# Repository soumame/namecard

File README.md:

# NFC Namecard/Badge

NFCによる給電（Energy Harvesting）を用いた、書き換え可能な電子ペーパー / NFCタグ / マイコンと、ファームウェア、Android・iOSアプリです。

Maker Faire Tokyo 2026のブース「そうまめの部屋」向けに製作しました。

## リポジトリ構成

- `namecard.kicad_sch` / `namecard.kicad_pcb` — KiCad回路図・基板設計
- [`production/`](production/) — Gerber、BOM、CPLなどの製造データ
- [`firmware/`](firmware/) — STM32ファームウェア
- [`client/android/`](client/android/) — Androidアプリ
- [`client/ios/`](client/ios/) — iOSアプリ（TestFlightベータ配布）
- [`iOS_development.md`](iOS_development.md) — iOS版の実装構成と今後の検証計画

Maker Faire Tokyo 2026向けの現行製造データは[`production/v5/`](production/v5/)にあります。JLCPCBへ入稿するファイルと注意点は同ディレクトリのREADMEを確認してください。

## Androidアプリのインストール

**[最新版のAndroidアプリ（namecard.apk）をダウンロード](https://github.com/soumame/namecard/releases/download/android-main/namecard.apk)**

利用にはAndroid 8.0以降のNFC対応端末が必要です。

1. 上のリンクから`namecard.apk`をダウンロードする
2. ブラウザからのインストールが止められた場合は、表示された設定画面で今回使用したブラウザからのインストールを許可する
3. 設定画面から戻り、`namecard.apk`をインストールする
4. インストール後、必要に応じてブラウザからのインストール許可をOFFへ戻す
5. アプリを開き、画像やテキストを編集してから`NFCに書込`を選び、完了するまで名刺を端末のNFCアンテナへ固定する

アップデートするときは、最新版APKを再度ダウンロードして既存アプリの上からインストールしてください。アプリを先にアンインストールすると、Libraryに保存した画像も削除されます。

このアプリが要求するAndroid権限はNFCのみです。リリースにはAPKと一緒にSHA-256チェックサムを掲載しています。[Releases](https://github.com/soumame/namecard/releases)の`android-main`は最新版で上書きされます。ソースの変更履歴は[コミット一覧](https://github.com/soumame/namecard/commits/main/)で確認できます。

うまく書き込めない場合は、スマートフォンのNFCアンテナ位置を確認し、ケースを外してからもう一度お試しください。書き込み中は名刺を動かしたり、ほかのアプリへ切り替えたりしないでください。

## iOSアプリ

iOS 17以降のNFC対応iPhone向けに、MameCardをTestFlightでベータ配布しています。

**[TestFlight事前登録フォームに回答する](https://forms.gle/RqQPmfoJ9aMMtRm66)**

フォームへの回答後に、TestFlightの参加リンクをお送りします。届いたリンクから案内に沿って
インストールしてください。名刺への書き込みには対応する名刺基板が必要です。

iPhone XR／iOS 18で白黒画像・URL設定・クリーニング・振動案内の動作報告を受けています。
ほかの機種での確認と給電・時間の計測を進めます。試す内容と報告方法は
[ベータ試験ガイド](client/ios/docs/BETA_TESTING.md)を参照してください。

4階調は編集・プレビュー・保存・BIN入出力に対応しますが、iOSからの4階調NFC書き込みと、
4階調表示からの白黒移行は無効です。販売済みの基板・FWの変更は不要です。
開発・配布の手順は[iOSアプリのREADME](client/ios/README.md)を参照してください。

## 開発状況について

詳しい開発状況は[ブログ記事](https://tokumaru.work/ja/tech/maker-faire-tokyo-2026/)をご確認ください。

## Q&A

### なんでアプリがPlay Storeで公開されていないの?

- 少量製作のハードウェア向けアプリであるため、現在は署名済みAPKをGitHub Releasesで公開しています。
- ソースコードもこのリポジトリで確認できます。

### iOS版はいつ使えるの?

- TestFlightでベータ版を利用できます。[事前登録フォーム](https://forms.gle/RqQPmfoJ9aMMtRm66)への回答後に、TestFlightの参加リンクをお送りします。実機検証後にApp Store公開を目指します。
- Apple Developer Programには登録済みです。現在の配布手順は[iOS配布ドキュメント](client/ios/docs/DISTRIBUTION.md)を参照してください。

### 1枚あたりの原価は？いくらで売るの？

- 部品の調達や製品の仕様次第ですが、30枚量産すると1枚あたり2500~3000円超えとなります。
  - たくさん発注すれば安くなるので、大量生産すれば2000~2500円くらいを狙えると考えています。
- それに自分の開発に使う道具の調達や時間を入れると、5000円くらいで売るのが妥当かなと考えています。

## ライセンス

このリポジトリで独自に作成したハードウェア設計、製造データ、ファームウェア、Android・iOSアプリ、文書は[MIT License](LICENSE)で提供します。自由に利用・改変・再配布できますが、著作権表示とライセンス表示を保持してください。

STM32Cube/CMSISやMaterial Symbolsなどの第三者著作物には、それぞれのライセンスが適用されます。詳細は[THIRD_PARTY_NOTICES.md](THIRD_PARTY_NOTICES.md)を確認してください。

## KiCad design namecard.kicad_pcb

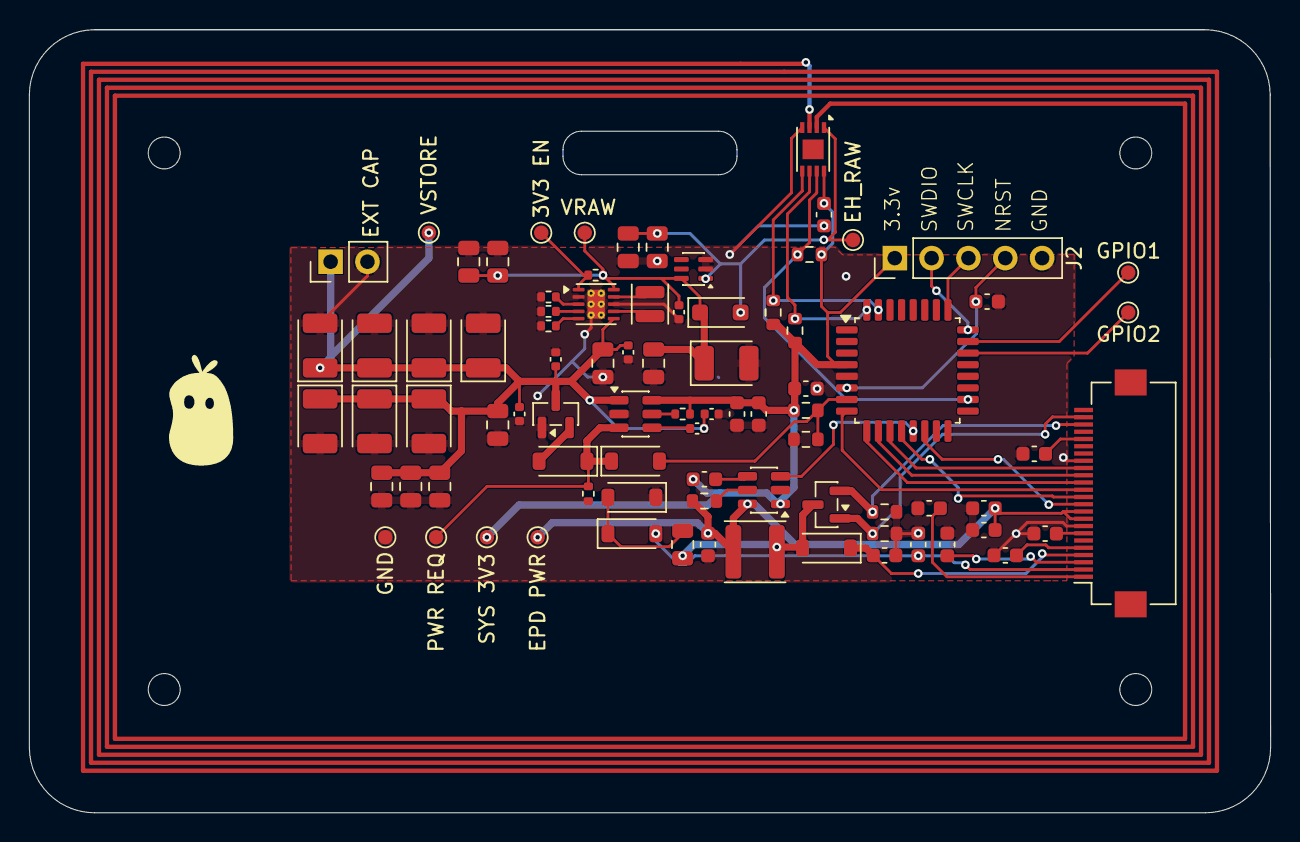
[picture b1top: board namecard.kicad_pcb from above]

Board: 2 copper layers, 85.6 x 54.0 mm, 84 parts (0 on the bottom side), 46 nets.

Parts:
3V3 EN: EN_3V3_TP; TestPoint_Pad_D1.0mm
C1, C2, C5, C6, C7, C9, C10, C11, C12: 1uF 50V X5R; C_0603_1608Metric
C3: 4.7uF 25V X5R; C_0805_2012Metric
C4: 4.7uF 16V X5R; C_0603_1608Metric
C8, C13: 0.1uF; C_0603_1608Metric
C14, C15, C16, C17: 220uF/6.3V; CP_EIA-3528-21_Kemet-B
C18, C20: 100nf; C_0603_1608Metric
C19: 1nF; C_0603_1608Metric
C23, C25: 1uf; C_0805_2012Metric
C24, C26: 0.1uf; C_0805_2012Metric
C27: 1nF; C_0402_1005Metric
C28, C41, C43, C44, C45: 100nF; C_0402_1005Metric
C29, C30, C31, C32, C42: 22uF 6.3V X5R; C_0805_2012Metric
C39: 220uF/6.3V VRAW; CP_EIA-3528-21_Kemet-B
C40: 10uF 25V X5R; C_0805_2012Metric
C46, C48, C49: 220uF/6.3V VRES; CP_EIA-3528-21_Kemet-B
C47: 100nF U2 DECOUPLING; C_0603_1608Metric
D1, D2, D3: MBR0530T1G; D_SOD-123
D4: DNP SCHOTTKY; D_SOD-123F
D5, D6: 1N4148W; D_SOD-123
EPD PWR: EPD_SW_TP; TestPoint_Pad_D1.0mm
EXT CAP: EXT_VRES_CAP_DNP; PinHeader_1x02_P2.54mm_Vertical
GND: TestPoint; TestPoint_Pad_D1.0mm
GPIO1, GPIO2: TestPoint; TestPoint_Pad_D1.0mm
J1: Conn_01x24; Hirose_FH12-24S-0.5SH_1x24-1MP_P0.50mm_Horizontal
J2: Conn_01x05; PinHeader_1x05_P2.54mm_Vertical
L1: 47uH; L_APV_ANR4020
L2: 2.2uH; L_Sunlord_SWPA252012S
PWR REQ: PWR_REQ_TP; TestPoint_Pad_D1.0mm
Q1: AO3400A; SOT-23
R1: 1M; R_0603_1608Metric
R2: 2.2R; R_0603_1608Metric
R3: 1M DNP; R_0603_1608Metric
R4, R6: 10k; R_0603_1608Metric
R5: 470k DNP; R_0603_1608Metric
R7: 4.7M; R_0402_1005Metric
R8: 1k; R_0402_1005Metric
R9: 36.5k 1%; R_0402_1005Metric
R10: 5.11k 1% (2.5mA); R_0402_1005Metric
R11: 16.2k 1%; R_0402_1005Metric
R12: 0R; R_0402_1005Metric
R13: 10k GPO PULLUP; R_0603_1608Metric
R14: 1k EPD DISCHARGE; R_0603_1608Metric
SYS 3V3: SYS_VDD_TP; TestPoint_Pad_D1.0mm
TP1: VRES_3V3_TP; TestPoint_Pad_D1.0mm
TP3: V_EH_RAW_TP; TestPoint_Pad_D1.0mm
U1: STM32G031K8T6; LQFP-32_7x7mm_P0.8mm
U2: ST25DV04K-IER6C3; DFN-8-1EP_3x2mm_P0.5mm_EP1.36x1.46mm
U3, U4: TPS22917DBV; SOT-23-6
U5: TPS3839K33DBZR; SOT-23
U6: LM66100; SOT-363_SC-70-6
U7: TPS63900; WSON-10-1EP_2.5x2.5mm_P0.5mm_EP1.2x2mm_ThermalVias
VRAW: VRAW_TP; TestPoint_Pad_D1.0mm

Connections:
/CFG1: R9.1, U7.3 (CFG1)
/CFG2: R10.1, U7.4 (CFG2)
/CFG3: R11.1, U7.5 (CFG3)
/EN_3V3: 3V3 EN.1 (1_1), R12.2, U7.1 (EN)
/EPD_BUSY: J1.16, U1.11 (PA4)
/EPD_CS: J1.13, U1.8 (PA1)
/EPD_DC: J1.14, U1.9 (PA2)
/EPD_RST: J1.15, U1.10 (PA3)
/EPD_SW: C4.1, C9.1, C18.2, EPD PWR.1 (1_1), J1.9, J1.10, L1.2, R14.2, U3.6 (VOUT)
/GDR: J1.23, Q1.1 (G), R1.1
/I2C_SCL: R6.1, U1.32 (PB8), U2.6 (SCL)
/I2C_SDA: R4.1, U1.31 (PB7), U2.5 (SDA)
/LX1: L2.1, U7.9 (LX1)
/LX2: L2.2, U7.7 (LX2)
/NFC_INT: R13.1, U1.18 (PA8), U2.7 (GPO)
/NRST: C13.1, J2.4, U1.6 (PF2-NRST)
/PREVGH: C5.2, D3.1 (K), J1.4
/PREVGL: C11.1, D1.2 (A), J1.2
/PWR_GOOD: D5.2 (A), U5.2 (~RESET)
/PWR_HOLD: D6.2 (A), R3.2, R5.1, U1.7 (PA0)
/PWR_REQ: D5.1 (K), D6.1 (K), PWR REQ.1 (1_1), R7.1, U4.3 (ON)
/RESE: J1.22, Q1.2 (S), R2.1
/SPI_MOSI: J1.11, U1.14 (PA7)
/SPI_SCK: J1.12, U1.12 (PA5)
/SWCLK: J2.3, U1.25 (PA14)
/SWDIO: J2.2, U1.24 (PA13)
/SYS_VDD: C1.1, C8.1, C19.2, C20.1, C47.1, J2.1, R3.1, R4.2, R6.2, R8.1, R13.2, SYS 3V3.1 (1_1), U1.4 (VDD), U2.8 (VCC), U3.1 (VIN), U4.6 (VOUT)
/U3_CT: C19.1, U3.4 (CT)
/U4_CT: C27.1, U4.4 (CT)
/U4_QOD: R8.2, U4.5 (QOD)
/VRAW: C25.1, C26.1, C39.1, C40.1, C41.1, D4.1 (K), R12.1, U6.6 (VOUT), U7.10 (VIN), VRAW.1 (1_1)
/VRES_3V3: C14.1, C15.1, C16.1, C17.1, C27.2, C28.1, C29.1, C30.1, C31.1, C32.1, C42.1, C43.1, C44.1, C45.1, C46.1, C48.1, C49.1, EXT CAP.1, TP1.1 (1_1), U4.1 (VIN), U5.3 (VDD), U7.6 (VOUT)
/V_EH_RAW: C23.1, C24.1, D4.2 (A), TP3.1 (1_1), U2.1 (V_EH), U6.1 (VIN)
GND: C1.2, C2.2, C4.2, C5.1, C6.2, C7.2, C8.2, C9.2, C10.2, C11.2, C12.1, C13.2, C14.2, C15.2, C16.2, C17.2, C18.1, C20.2, C23.2, C24.2, C25.2, C26.2, C28.2, C29.2, C30.2, C31.2, C32.2, C39.2, C40.2, C41.2, C42.2, C43.2, C44.2, C45.2, C46.2, C47.2, C48.2, C49.2, D2.1 (K), EXT CAP.2, GND.1 (1_1), J1.8, J1.17, J2.5, R1.2, R2.2, R5.2, R7.2, R9.2, R10.2, R11.2, U1.5 (VSS), U2.4 (VSS), U3.2 (GND), U4.2 (GND), U5.1 (GND), U6.2 (GND), U6.3 (~CE), U7.2 (SEL), U7.8 (GND), U7.11 (GND)
unnamed: C3.1, D1.1 (K), D2.2 (A)
unnamed: C3.2, D3.2 (A), L1.1, Q1.3 (D)
unnamed: C12.2, J1.1
unnamed: C10.1, J1.3
unnamed: C7.1, J1.5
unnamed: C6.1, J1.7
unnamed: C2.1, J1.20
unnamed: U1.13 (PA6), U3.3 (ON)
unnamed: GPIO2.1 (1_1), U1.22 (PA9/PA11)
unnamed: GPIO1.1 (1_1), U1.23 (PA10/PA12)
unnamed: U2.2 (AC0), U2.3 (AC1)
unnamed: R14.1, U3.5 (QOD)

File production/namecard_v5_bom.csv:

Designator,Footprint,Quantity,Value,LCSC Part #
"C1, C10, C11, C12, C2, C5, C6, C7, C9",0603,9,1uF 50V X5R,C15849
"C13, C8",0603,2,0.1uF,C14663
"C14, C15, C16, C17",CP_EIA-3528-21_Kemet-B,4,220uF/6.3V,C30242
"C18, C20",0603,2,100nf,C14663
C19,0603,1,1nF,C1588
"C23, C25",0805,2,1uf,C28323
"C24, C26",0805,2,0.1uf,C28233
C27,0402,1,1nF,C1523
"C28, C41, C43, C44, C45",0402,5,100nF,C1525
"C29, C30, C31, C32, C42",0805,5,22uF 6.3V X5R,C5674
C3,0805,1,4.7uF 25V X5R,C722528
C39,CP_EIA-3528-21_Kemet-B,1,220uF/6.3V VRAW,C30242
C4,0603,1,4.7uF 16V X5R,C19666
C40,0805,1,10uF 25V X5R,C5137488
"C46, C48, C49",CP_EIA-3528-21_Kemet-B,3,220uF/6.3V VRES,C30242
C47,0603,1,100nF U2 DECOUPLING,C14663
"D1, D2, D3",D_SOD-123,3,MBR0530T1G,C82046
"D5, D6",D_SOD-123,2,1N4148W,C47117477
J1,Hirose_FH12-24S-0.5SH_1x24-1MP_P0.50mm_Horizontal,1,Conn_01x24,C506794
J2,PinHeader_1x05_P2.54mm_Vertical,1,Conn_01x05,C5156614
L1,L_APV_ANR4020,1,47uH,C6364799
L2,L_Sunlord_SWPA252012S,1,2.2uH,C23894
Q1,SOT-23,1,AO3400A,C20917
R1,0603,1,1M,C22935
R10,0402,1,5.11k 1% (2.5mA),C274895
R11,0402,1,16.2k 1%,C27176
R12,0402,1,0R,C17168
R13,0603,1,10k GPO PULLUP,C25804
R14,0603,1,1k EPD DISCHARGE,C21190
R2,0603,1,2.2R,C22939
"R4, R6",0603,2,10k,C25804
R7,0402,1,4.7M,C3013173
R8,0402,1,1k,C11702
R9,0402,1,36.5k 1%,C25887
U1,LQFP-32_7x7mm_P0.8mm,1,STM32G031K8T6,C432203
U2,DFN-8-1EP_3x2mm_P0.5mm_EP1.36x1.46mm,1,ST25DV04K-IER6C3,C2908287
"U3, U4",SOT-23-6,2,TPS22917DBV,C2681320
U5,SOT-23,1,TPS3839K33DBZR,C96333
U6,SOT-363_SC-70-6,1,LM66100,C2869734
U7,WSON-10-1EP_2.5x2.5mm_P0.5mm_EP1.2x2mm_ThermalVias,1,TPS63900,C1518762

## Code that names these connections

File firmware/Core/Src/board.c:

#include "board.h"

static volatile bool epd_busy_edge;
static volatile bool nfc_gpo_edge;
static volatile bool brownout_latched;

void board_early_power_safe(void)
{
    RCC->IOPENR |= RCC_IOPENR_GPIOAEN;
    (void)RCC->IOPENR;

    /* Preload PA0 high before enabling its output driver so the TPS22917
       self-hold path cannot glitch low.  PA6 is preloaded low to keep the EPD
       rail off throughout C/HAL initialization. */
    GPIOA->BSRR = PWR_HOLD_PIN | ((uint32_t)EPD_POWER_EN_PIN << 16U);
    GPIOA->OTYPER &= ~(GPIO_OTYPER_OT0 | GPIO_OTYPER_OT6);
    GPIOA->PUPDR &= ~((3UL << (0U * 2U)) | (3UL << (6U * 2U)));
    GPIOA->MODER =
        (GPIOA->MODER & ~((3UL << (0U * 2U)) | (3UL << (6U * 2U)))) |
        (1UL << (0U * 2U)) | (1UL << (6U * 2U));
}

void board_epd_bus_hiz(void)
{
    GPIO_InitTypeDef gpio = {0};
    gpio.Pin = EPD_CS_PIN | EPD_DC_PIN | EPD_RST_PIN | EPD_SCK_PIN | EPD_MOSI_PIN;
    gpio.Mode = GPIO_MODE_ANALOG;
    gpio.Pull = GPIO_NOPULL;
    HAL_GPIO_Init(GPIOA, &gpio);
}

void board_epd_bus_active(void)
{
    GPIO_InitTypeDef gpio = {0};

    HAL_GPIO_WritePin(GPIOA, EPD_CS_PIN, GPIO_PIN_SET);
    HAL_GPIO_WritePin(GPIOA, EPD_DC_PIN, GPIO_PIN_RESET);
    HAL_GPIO_WritePin(GPIOA, EPD_RST_PIN, GPIO_PIN_SET);
    gpio.Pin = EPD_CS_PIN | EPD_DC_PIN | EPD_RST_PIN;
    gpio.Mode = GPIO_MODE_OUTPUT_PP;
    gpio.Pull = GPIO_NOPULL;
    gpio.Speed = GPIO_SPEED_FREQ_LOW;
    HAL_GPIO_Init(GPIOA, &gpio);

    gpio.Pin = EPD_SCK_PIN | EPD_MOSI_PIN;
    gpio.Mode = GPIO_MODE_AF_PP;
    gpio.Pull = GPIO_NOPULL;
    gpio.Speed = GPIO_SPEED_FREQ_LOW;
    gpio.Alternate = GPIO_AF0_SPI1;
    HAL_GPIO_Init(GPIOA, &gpio);
}

void board_gpio_init(void)
{
    __HAL_RCC_GPIOA_CLK_ENABLE();
    __HAL_RCC_GPIOB_CLK_ENABLE();

    HAL_GPIO_WritePin(PWR_HOLD_PORT, PWR_HOLD_PIN, GPIO_PIN_SET);
    HAL_GPIO_WritePin(EPD_POWER_EN_PORT, EPD_POWER_EN_PIN, GPIO_PIN_RESET);
    GPIO_InitTypeDef gpio = {0};
    gpio.Pin = PWR_HOLD_PIN | EPD_POWER_EN_PIN;
    gpio.Mode = GPIO_MODE_OUTPUT_PP;
    gpio.Pull = GPIO_NOPULL;
    gpio.Speed = GPIO_SPEED_FREQ_LOW;
    HAL_GPIO_Init(EPD_POWER_EN_PORT, &gpio);

    gpio.Pin = EPD_BUSY_PIN;
    gpio.Mode = GPIO_MODE_IT_RISING_FALLING;
    gpio.Pull = GPIO_NOPULL;
    HAL_GPIO_Init(EPD_BUSY_PORT, &gpio);

    gpio.Pin = NFC_GPO_PIN;
    gpio.Mode = GPIO_MODE_IT_RISING_FALLING;
    gpio.Pull = GPIO_NOPULL;
    HAL_GPIO_Init(NFC_GPO_PORT, &gpio);

    board_epd_bus_hiz();
    HAL_NVIC_SetPriority(EXTI4_15_IRQn, 2U, 0U);
    HAL_NVIC_EnableIRQ(EXTI4_15_IRQn);
}

HAL_StatusTypeDef board_power_guard_init(void)
{
    PWR_PVDTypeDef pvd = {0};
    pvd.PVDLevel = PWR_PVDLEVEL_4;
    pvd.Mode = PWR_PVD_MODE_IT_FALLING;

    brownout_latched = false;
    __HAL_PWR_PVD_EXTI_CLEAR_RISING_FLAG();
    __HAL_PWR_PVD_EXTI_CLEAR_FALLING_FLAG();
    if (HAL_PWREx_ConfigPVD(&pvd) != HAL_OK) {
        return HAL_ERROR;
    }
    HAL_NVIC_SetPriority(PVD_IRQn, 0U, 0U);
    HAL_NVIC_EnableIRQ(PVD_IRQn);
    HAL_PWREx_EnablePVD();
    HAL_Delay(1U); /* PVD startup is at most a few microseconds. */
    if (__HAL_PWR_GET_FLAG(PWR_FLAG_PVDO)) {
        board_brownout_shutdown_isr();
        return HAL_ERROR;
    }
    return HAL_OK;
}

void board_power_hold_enable(void)
{
    HAL_GPIO_WritePin(PWR_HOLD_PORT, PWR_HOLD_PIN, GPIO_PIN_SET);
}

void board_power_hold_release(void)
{
    HAL_GPIO_WritePin(PWR_HOLD_PORT, PWR_HOLD_PIN, GPIO_PIN_RESET);
}

void board_brownout_shutdown_isr(void)
{
    const uint32_t epd_bus_mode_mask =
        (3UL << (1U * 2U)) | (3UL << (2U * 2U)) |
        (3UL << (3U * 2U)) | (3UL << (5U * 2U)) |
        (3UL << (7U * 2U));

    brownout_latched = true;
    GPIOA->BSRR = (uint32_t)EPD_POWER_EN_PIN << 16U;
    GPIOA->MODER |= epd_bus_mode_mask; /* Analog/no-pull: no EPD back-power. */
    GPIOA->BSRR = (uint32_t)PWR_HOLD_PIN << 16U;
    __DSB();
}

bool board_brownout_detected(void)
{
    return brownout_latched;
}

void board_epd_power_on(void)
{
    if (!brownout_latched) {
        HAL_GPIO_WritePin(EPD_POWER_EN_PORT, EPD_POWER_EN_PIN, GPIO_PIN_SET);
    }
}

void board_epd_power_off(void)
{
    board_epd_bus_hiz();
    HAL_GPIO_WritePin(EPD_POWER_EN_PORT, EPD_POWER_EN_PIN, GPIO_PIN_RESET);
}

bool board_epd_is_busy(void)
{
    return HAL_GPIO_ReadPin(EPD_BUSY_PORT, EPD_BUSY_PIN) == GPIO_PIN_SET;
}

void board_note_epd_busy_edge(void)
{
    epd_busy_edge = true;
}

void board_note_nfc_gpo_edge(void)
{
    nfc_gpo_edge = true;
}

bool board_take_epd_busy_edge(void)
{
    const bool value = epd_busy_edge;
    epd_busy_edge = false;
    return value;
}

bool board_take_nfc_gpo_edge(void)
{
    const bool value = nfc_gpo_edge;
    nfc_gpo_edge = false;
    return value;
}

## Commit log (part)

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2026-04-19 Initial commit: KiCad project start
2026-04-19 電源回路周りの調整
2026-04-25 基盤配置の調整
2026-04-25 電源の太さの調整
2026-04-25 v2 production
2026-05-02 V3向けの変更:LEDの向きを直したり
2026-05-12 wip: 電源周りの回路図を更新
2026-05-13 wip: v3向けに配置を更新
2026-05-14 wip: 配置を更新
